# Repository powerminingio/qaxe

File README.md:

# Compatible replacement parts for ++

[25MHz Oscillator](https://www.digikey.de/de/products/detail/iqd-frequency-products/LFSPXO076024/8633951?s=N4IgTCBcDaIIwE4wGYC0cBsGAs7UDkAREAXQF8g), Replacement: [OXLTDLJANF-25.000000](https://www.digikey.de/de/products/detail/taitien/OXLTDLJANF-25-000000/13235309?srsltid=AfmBOopcMDw-7vaDW7fInywY2qr_aMaeX0WMDV0aphwuDXjSpvlEyQxF)<br/>

# Compatible replacement parts for ++ and +

[0.8V LDO](https://www.digikey.de/de/products/detail/microchip-technology/MCP1824T-0802E-OT/1635455), Replacement: [TPS78408QDBVRQ1](https://www.digikey.com/en/products/detail/texas-instruments/TPS78408QDBVRQ1/13563052)

# NerdQAxe++ Powermining revision

Few improvements for revision that we manufacture

## Features

- Car Minifuse
- 180nH inductors (Eliminates frying VRM)
- Level shifter pull-ups
- LGA115* (75x75mm) mounting pattern
- LGA2011 Narrow ILM (94x56mm) mounting pattern

**rev6.1PM**

# NerdQAxe+

NerdQaxe+ is a Qaxe+ with [Nerdminer](https://github.com/BitMaker-hub/NerdMiner_v2) / [Nerdaxe](https://github.com/BitMaker-hub/NerdAxeUltra) Display and is running the [BitAxe](https://github.com/skot/bitaxe) Firmware as its core.

It runs standalone without Raspberry Pi and uses 4 ASICs of type BM1368.

Highlights:

- uses the NerdAxe / NerdMiner display
- better Buck converter that runs a lot cooler (about 10°C) with oltage / current / power monitoring
- standalone, no Raspberry Pi or other PC needed
- AxeOS with improvements and enhancements
  - Influx DB support
  - Better charting (10m, 1h, 1d), data doesn't get lost on Web UI reloads 
  - ASIC clock and voltage adjustable without reboot
  - Stratum client stability improvements (TCP timeouts)

The NerdQAxe+ runs with a variant of the AxeOS firmware: https://github.com/shufps/ESP-Miner-NerdQAxePlus

**rev5.0** Good to go, no bug found 🥳🚀

# QAxe+

QAxe+ is a quad-BM1368 Variant. Mining speed is average 2.4TH/s at 55W (measured at 230V)<br>

<br>

**rev4:** QAxe+ with BM1368, working but ASIC reset behaves weird sometimes. Measured performance is 2.4TH/s average with 55W (measured on 230V)<br>
**rev4.1:** only change is 3 pull-down resistors on NRSTI pins<br>
<br>

# Qaxe

Qaxe is a  quad-BM1366 Miner based on the [PiAxe](https://github.com/shufps/piaxe) and [BitAxe](https://github.com/skot/bitaxe/tree/ultra-v1.3).

**rev1:** is tested and operating at about 1.7TH/s average speed.<br>
**rev2:** working fine with the expected speed of ~1.8TH/s avg after some minor modifications (330µF caps are wrongly placed, see rev3)<br>
**rev3:** Fixed Caps placement and added Boot-Switch. It should put the STM32 into DFU bootloader but not tested yet.<br>
**rev3.1:** Added pulldown on PB2 that is needed for booting the USB bootloader<br>
**rev3.2:** Board got 3mm larger for a perfect fit of low-profile coolers<br>
<br>
**note**: If you have a board with `BOOT`-button (any rev3) please order the L072 STM32 (BOM has been updated) because usb bootloader is the easiest way to flash the STM.<br>

ASICs
=====

The QAxe uses 4 ASICs of type BM1366.

The QAxe+ and NerdQaxe+ uses 4 ASICs of type BM1368.

Compilation (Bootloader or CMSIS-DAP) (QAxe, QAxe+)
======================================

## Dockered compilation and flashing
There is a wonderfull Docker based single-script compilation and flash tool for the QAxe Firmware:

https://github.com/AnimaI/QAxe-Docker-Bootloader

## Manual compilation and installation

```bash
# install curl
sudo apt install curl

# install rust
curl --proto '=https' --tlsv1.2 https://sh.rustup.rs -sSf | sh

# add to ~/.bash.rc (afterwards, opening a new terminal is needed)
echo 'source "$HOME/.cargo/env"' >> ~/.bashrc

# clone repository
git clone https://github.com/shufps/qaxe

# clone submodules
cd qaxe
git submodule init
git submodule update

# add rust target for STM32L0 variants
rustup target add thumbv6m-none-eabi

# or add rust target for STM32L1 variants
#rustup target add thumbv7m-none-eabi

# build firmware for L072
cd firmware/fw-L072CB
./build.sh
```

## Installation via USB Bootloader on board with `BOOT` button (QAxe, QAxe+)
The STM32L072CB variant has an integrated DFU Bootloader that starts when pressing the `BOOT` button during reset.

Afterwards the firmware can be flashed via `dfu-utils`:

```bash
# install cargo-binutils and llvm tools
cargo install cargo-binutils
rustup component add llvm-tools-preview

# create the firmware.bin
DEFMT_LOG=info cargo objcopy --release --bin qaxe -- -O binary qaxe.bin

# install dfu-utils
sudo apt-get install dfu-util

now start the stm32 in DFU mode by pressing `boot` (only works with the STM32L072CB variant)

# after booting, list the devices
dfu-util --list

# flash the binary
dfu-util -a 0 -s 0x08000000:leave -D qaxe.bin
```

Mining Client (QAxe, QAxe+)
=============

Stratum Mining Client:<br>
https://github.com/shufps/piaxe-miner

Misc
====
If you like this project and want to support future work, feel free to donate to:
`bc1q7n70rumyv6lvu8avpml0c3uggvssfu52egum3q`

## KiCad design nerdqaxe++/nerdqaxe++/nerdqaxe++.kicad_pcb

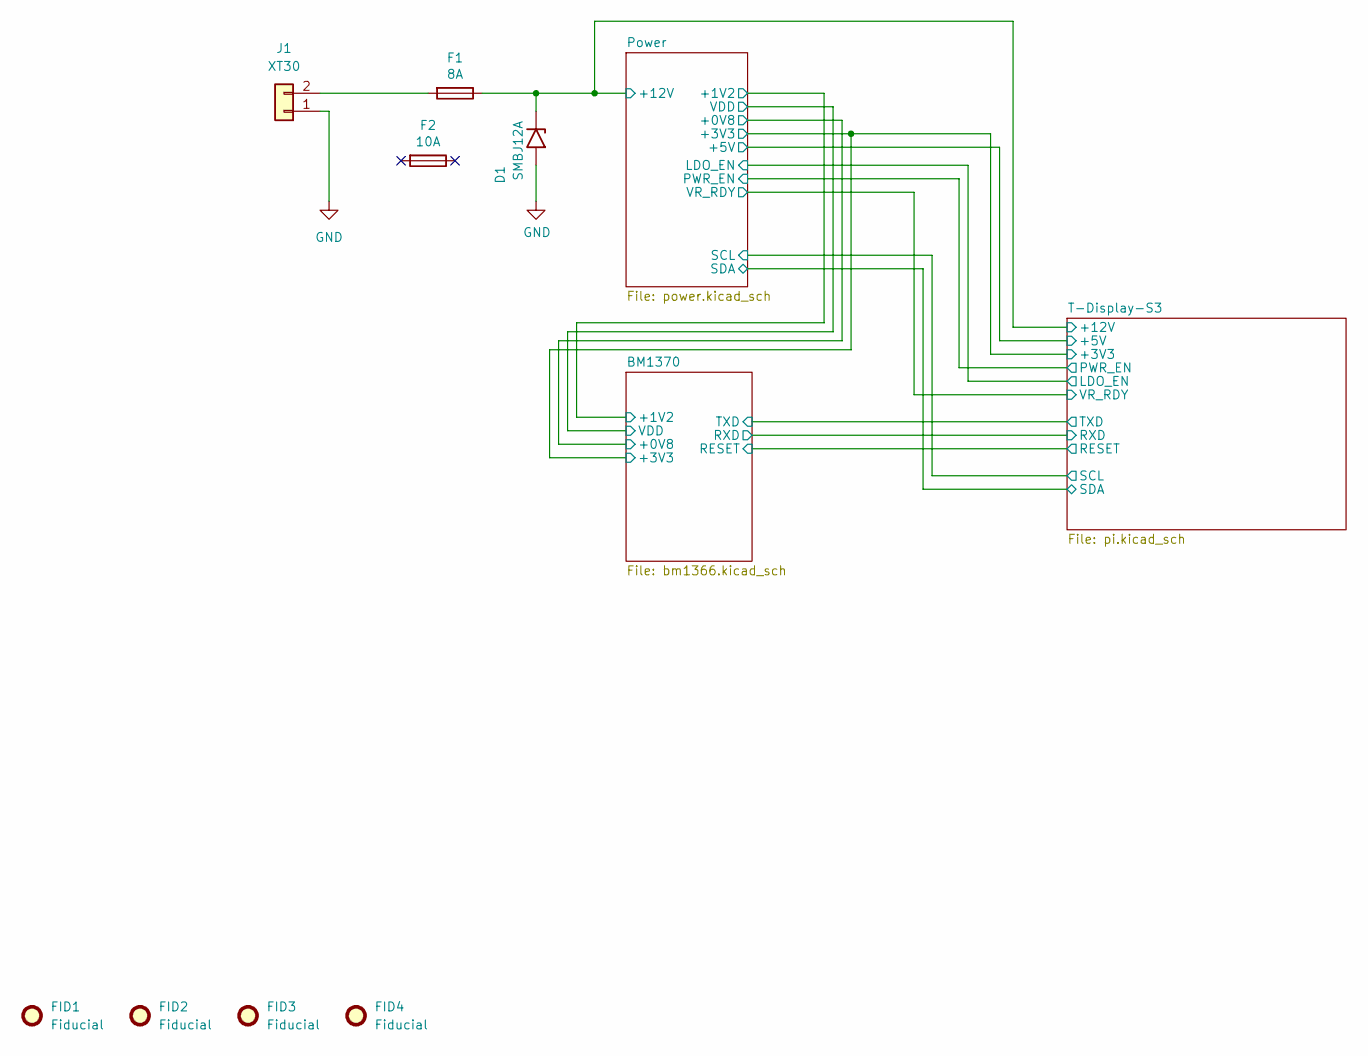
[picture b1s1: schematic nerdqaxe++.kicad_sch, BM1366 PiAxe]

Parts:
D1: SMBJ12A; D_SMB
F1: 8A; Fuseholder_Blade_Mini_Keystone_3568
F2: 10A
FID1, FID2, FID3, FID4: Fiducial; Fiducial_1mm_Mask2mm
J1: XT30; AMASS_XT30PW-M_1x02_P2.50mm_Horizontal

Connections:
+12V: D1.1 (A1), F1.1; also elsewhere on the board
GND: D1.2 (A2), J1.1; also elsewhere on the board
unnamed: F1.2, J1.2

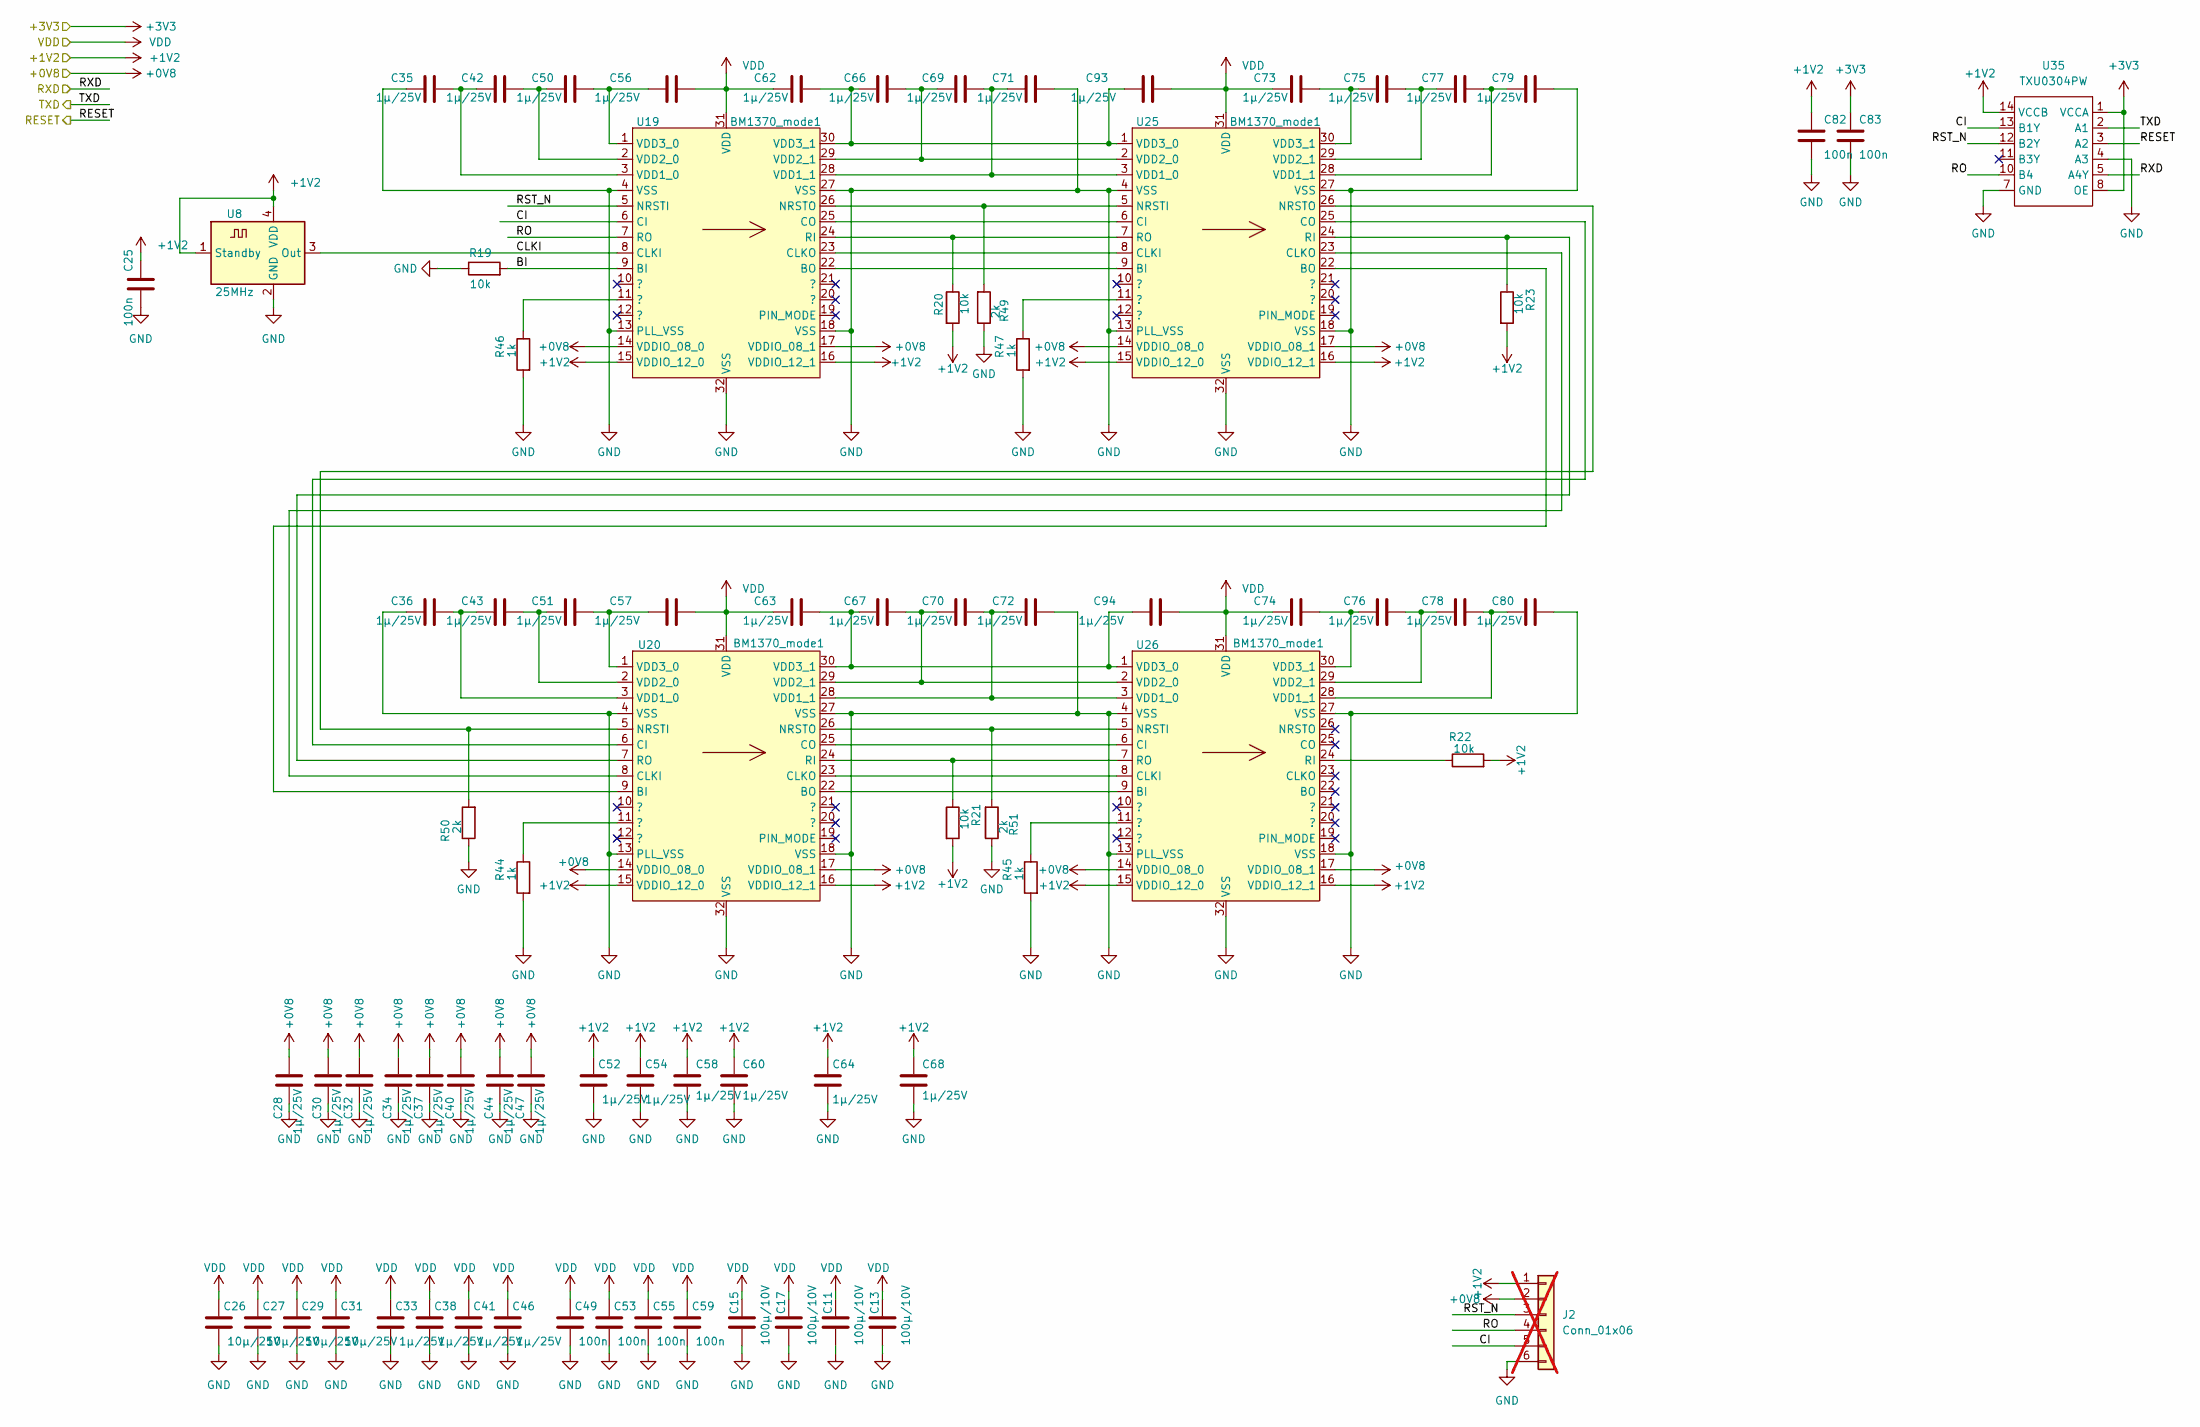
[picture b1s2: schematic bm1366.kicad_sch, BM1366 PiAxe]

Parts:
C11, C13, C15, C17: 100µ/10V; C_1210_3225Metric
C25, C49, C53, C55, C59, C82, C83: 100n; C_0805_2012Metric
C26, C27, C29, C31: 10µ/25V; C_0805_2012Metric
C28, C30, C32, C33, C34, C35, C36, C37, C38, C40, C41, C42, C43, C44, C46, C47, C50, C51, C52, C54, C56, C57, C58, C60, C62, C63, C64, C66, C67, C68, C69, C70, C71, C72, C73, C74, C75, C76, C77, C78, C79, C80, C93, C94: 1µ/25V; C_0805_2012Metric
J2: Conn_01x06; PinHeader_1x06_P1.27mm_Vertical; not fitted
R19, R20, R21, R22, R23: 10k; R_0805_2012Metric
R44, R45, R46, R47: 1k; R_0805_2012Metric
R49, R50, R51: 2k; R_0805_2012Metric
U8: 25MHz; Oscillator_SMD_EuroQuartz_XO32-4Pin_3.2x2.5mm
U19, U20, U25, U26: BM1370_mode1; BM1370_JB
U35: TXU0304PW; TSSOP-14_4.4x5mm_P0.65mm

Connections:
+0V8: C28.2, C30.2, C32.2, C34.2, C37.2, C40.2, C44.2, C47.2, J2.2, U19.14 (VDDIO_08_0), U19.17 (VDDIO_08_1), U20.14 (VDDIO_08_0), U20.17 (VDDIO_08_1), U25.14 (VDDIO_08_0), U25.17 (VDDIO_08_1), U26.14 (VDDIO_08_0), U26.17 (VDDIO_08_1); also elsewhere on the board
+1V2: C25.1, C52.1, C54.1, C58.1, C60.1, C64.1, C68.1, C82.1, J2.1, R20.2, R21.2, R22.2, R23.2, U8.1 (Standby), U8.4 (VDD), U19.15 (VDDIO_12_0), U19.16 (VDDIO_12_1), U20.15 (VDDIO_12_0), U20.16 (VDDIO_12_1), U25.15 (VDDIO_12_0), U25.16 (VDDIO_12_1), U26.15 (VDDIO_12_0), U26.16 (VDDIO_12_1), U35.14 (VCCB); also elsewhere on the board
+3V3: C83.1, U35.1 (VCCA), U35.8 (OE); also elsewhere on the board
/BM1370/BI: R19.2, U19.9 (BI)
/BM1370/CI: J2.5, U19.6 (CI), U35.13 (B1Y)
/BM1370/CLKI: U8.3 (Out), U19.8 (CLKI)
/BM1370/RESET: U35.3 (A2); also elsewhere on the board
/BM1370/RO: J2.4, U19.7 (RO), U35.10 (B4)
/BM1370/RST_N: J2.3, U19.5 (NRSTI), U35.12 (B2Y)
/BM1370/RXD: U35.5 (A4Y); also elsewhere on the board
/BM1370/TXD: U35.2 (A1); also elsewhere on the board
GND: C11.2, C13.2, C15.2, C17.2, C25.2, C26.2, C27.2, C28.1, C29.2, C30.1, C31.2, C32.1, C33.2, C34.1, C35.1, C36.1, C37.1, C38.2, C40.1, C41.2, C44.1, C46.2, C47.1, C49.2, C52.2, C53.2, C54.2, C55.2, C58.2, C59.2, C60.2, C64.2, C68.2, C71.2, C72.2, C79.2, C80.2, C82.2, C83.2, J2.6, R19.1, R44.2, R45.2, R46.2, R47.2, R49.1, R50.1, R51.1, U8.2 (GND), U19.4 (VSS), U19.13 (PLL_VSS), U19.18 (VSS), U19.27 (VSS), U19.32 (VSS), U20.4 (VSS), U20.13 (PLL_VSS), U20.18 (VSS), U20.27 (VSS), U20.32 (VSS), U25.4 (VSS), U25.13 (PLL_VSS), U25.18 (VSS), U25.27 (VSS), U25.32 (VSS), U26.4 (VSS), U26.13 (PLL_VSS), U26.18 (VSS), U26.27 (VSS), U26.32 (VSS), U35.4 (A3), U35.7 (GND); also elsewhere on the board
unnamed: R44.1, U20.11 (?)
unnamed: R45.1, U26.11 (?)
unnamed: R46.1, U19.11 (?)
unnamed: R47.1, U25.11 (?)
unnamed: U19.22 (BO), U25.9 (BI)
unnamed: U19.23 (CLKO), U25.8 (CLKI)
unnamed: U19.25 (CO), U25.6 (CI)
unnamed: R49.2, U19.26 (NRSTO), U25.5 (NRSTI)
unnamed: R20.1, U19.24 (RI), U25.7 (RO)
unnamed: C35.2, C42.1, U19.3 (VDD1_0)
unnamed: C69.2, C71.1, U19.28 (VDD1_1), U25.3 (VDD1_0)
unnamed: C42.2, C50.1, U19.2 (VDD2_0)
unnamed: C66.2, C69.1, U19.29 (VDD2_1), U25.2 (VDD2_0)
unnamed: C50.2, C56.1, U19.1 (VDD3_0)
unnamed: C62.2, C66.1, C93.1, U19.30 (VDD3_1), U25.1 (VDD3_0)
unnamed: U20.9 (BI), U25.22 (BO)
unnamed: U20.22 (BO), U26.9 (BI)
unnamed: U20.6 (CI), U25.25 (CO)
unnamed: U20.8 (CLKI), U25.23 (CLKO)
unnamed: U20.23 (CLKO), U26.8 (CLKI)
unnamed: U20.25 (CO), U26.6 (CI)
unnamed: R50.2, U20.5 (NRSTI), U25.26 (NRSTO)
unnamed: R51.2, U20.26 (NRSTO), U26.5 (NRSTI)
unnamed: R21.1, U20.24 (RI), U26.7 (RO)
unnamed: R23.1, U20.7 (RO), U25.24 (RI)
unnamed: C36.2, C43.1, U20.3 (VDD1_0)
unnamed: C70.2, C72.1, U20.28 (VDD1_1), U26.3 (VDD1_0)
unnamed: C43.2, C51.1, U20.2 (VDD2_0)
unnamed: C67.2, C70.1, U20.29 (VDD2_1), U26.2 (VDD2_0)
unnamed: C51.2, C57.1, U20.1 (VDD3_0)
unnamed: C63.2, C67.1, C94.1, U20.30 (VDD3_1), U26.1 (VDD3_0)
unnamed: C77.2, C79.1, U25.28 (VDD1_1)
unnamed: C75.2, C77.1, U25.29 (VDD2_1)
unnamed: C73.2, C75.1, U25.30 (VDD3_1)
unnamed: R22.1, U26.24 (RI)
unnamed: C78.2, C80.1, U26.28 (VDD1_1)
unnamed: C76.2, C78.1, U26.29 (VDD2_1)
unnamed: C74.2, C76.1, U26.30 (VDD3_1)
VDD: C11.1, C13.1, C15.1, C17.1, C26.1, C27.1, C29.1, C31.1, C33.1, C38.1, C41.1, C46.1, C49.1, C53.1, C55.1, C56.2, C57.2, C59.1, C62.1, C63.1, C73.1, C74.1, C93.2, C94.2, U19.31 (VDD), U20.31 (VDD), U25.31 (VDD), U26.31 (VDD); also elsewhere on the board

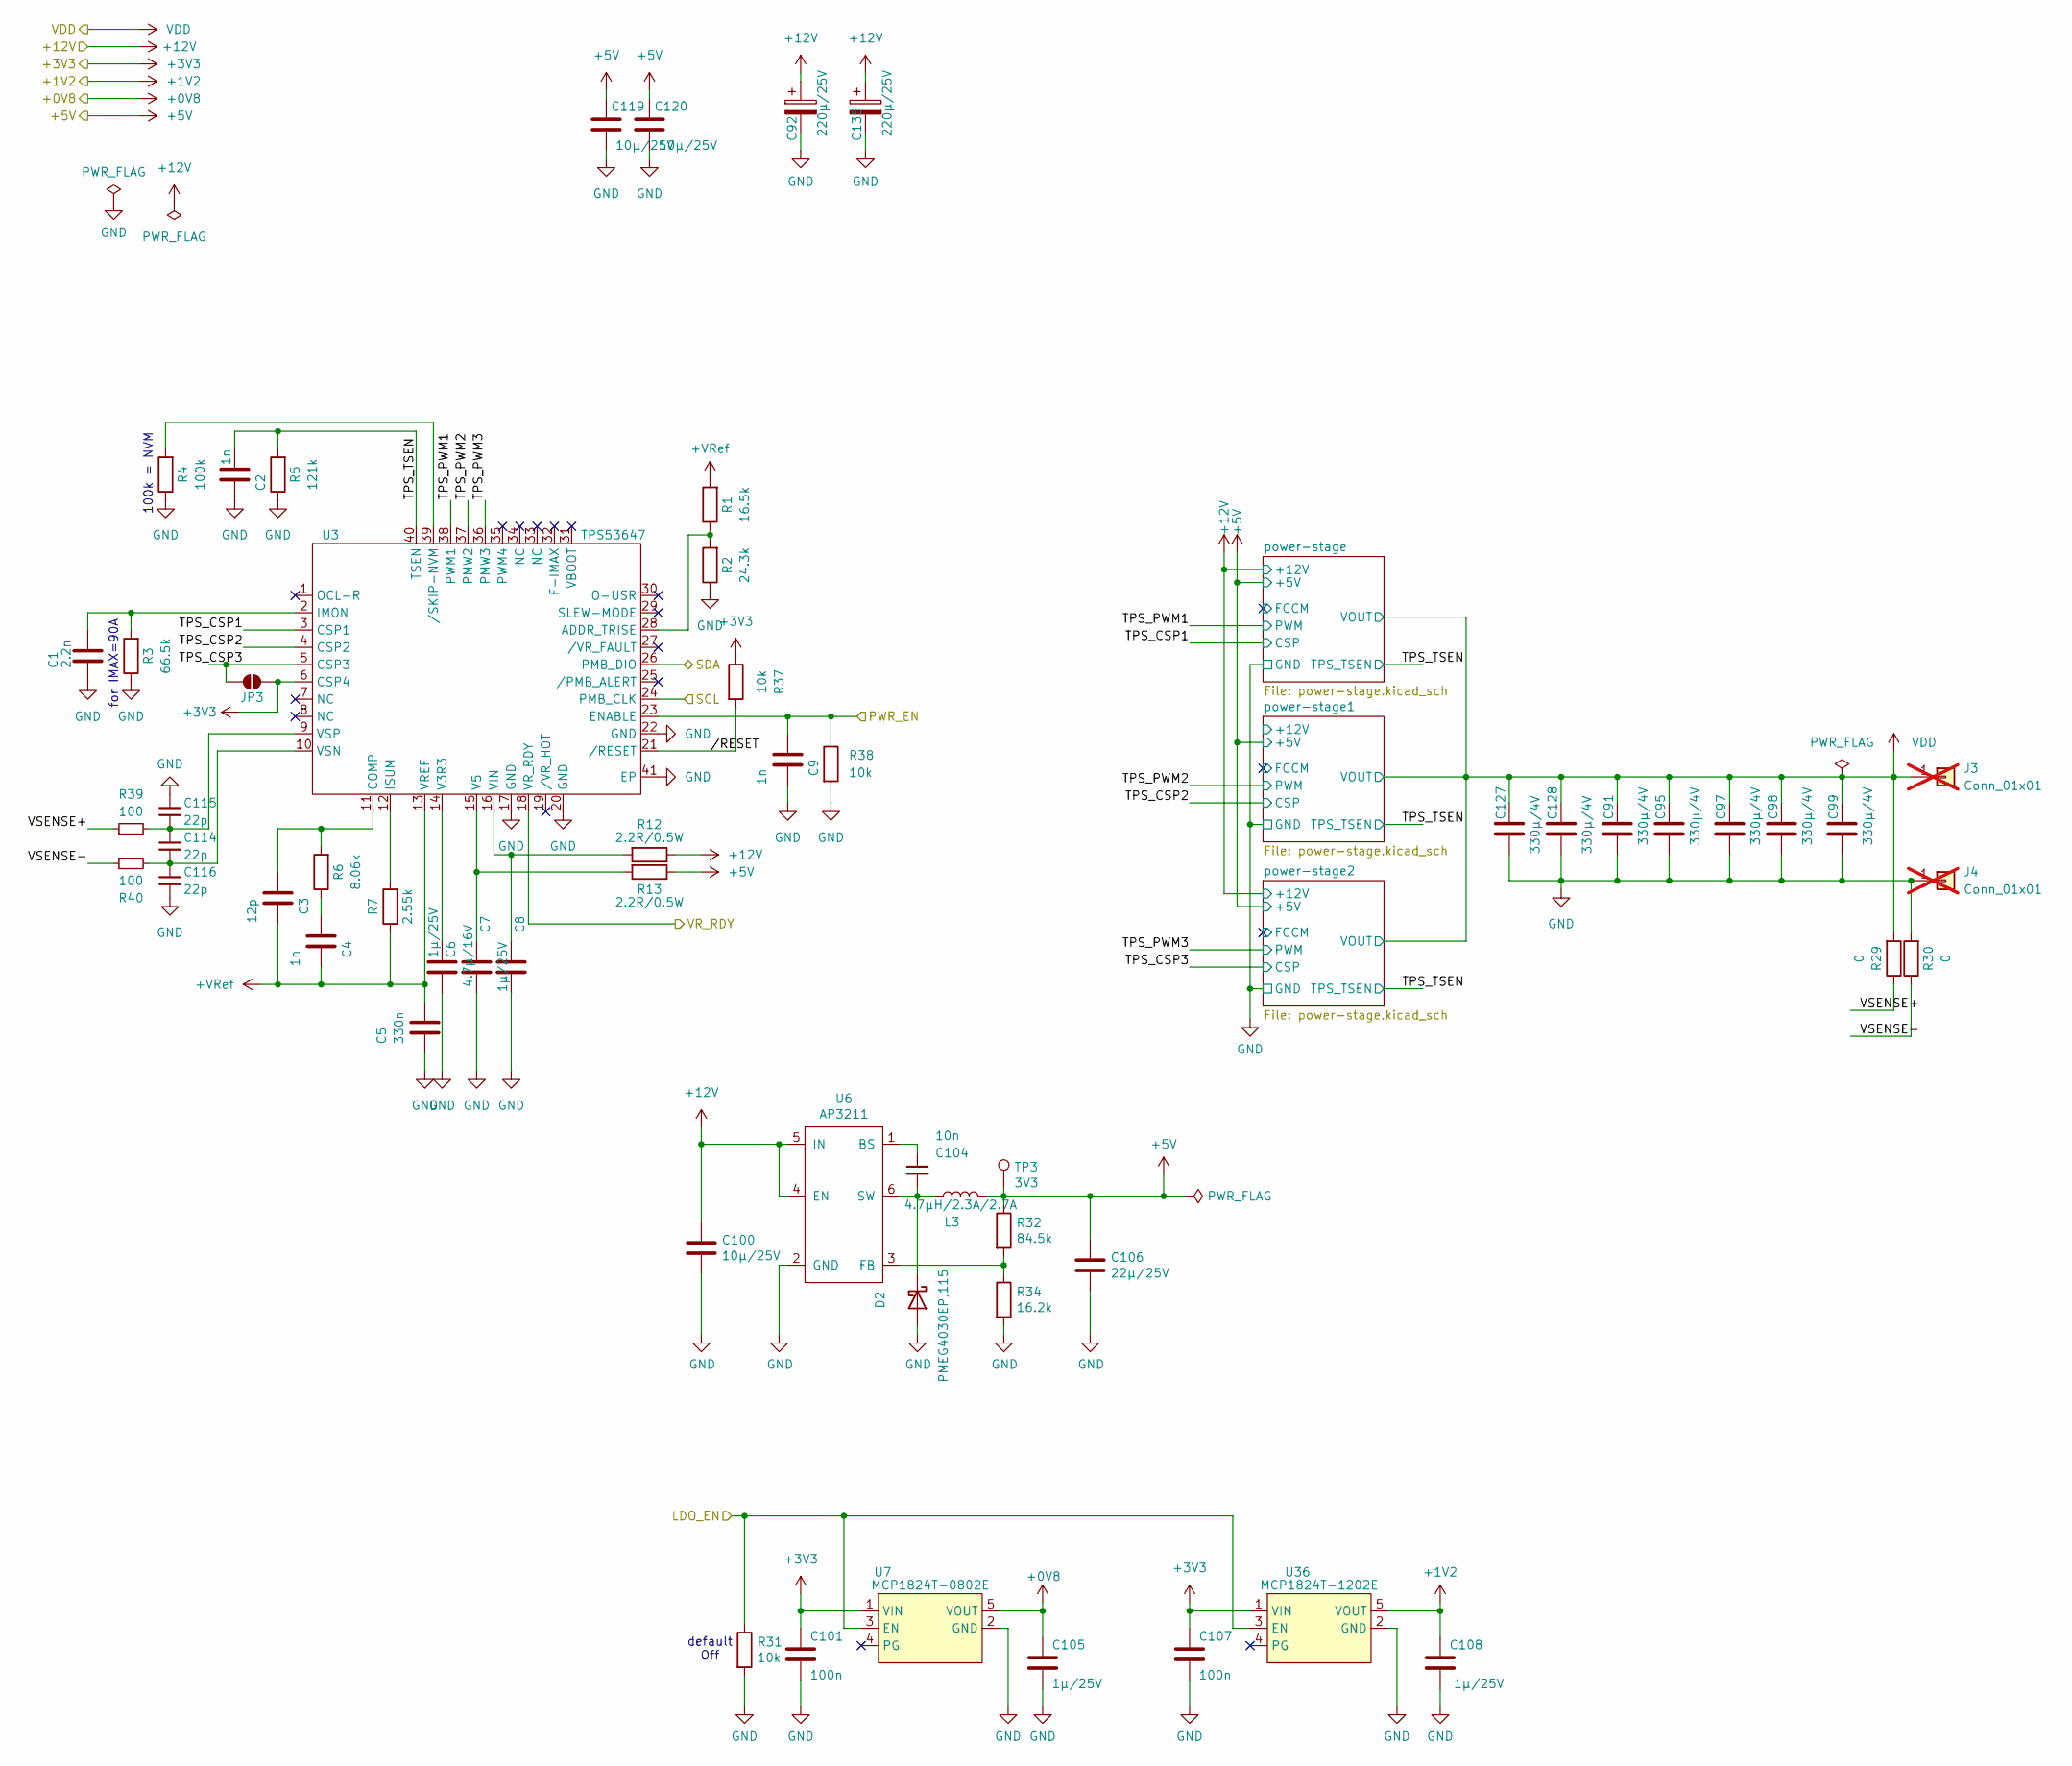
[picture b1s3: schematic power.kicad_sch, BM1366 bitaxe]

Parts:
C1: 2.2n; C_0805_2012Metric
C2, C4, C9: 1n; C_0805_2012Metric
C3: 12p; C_0603_1608Metric
C5: 330n; C_0805_2012Metric
C6, C8, C105, C108: 1µ/25V; C_0805_2012Metric
C7: 4.7µ/16V; C_0805_2012Metric
C91, C95, C97, C98, C99, C127, C128: 330µ/4V; C_1210_3225Metric
C92, C135: 220µ/25V; CP_Elec_8x10
C100, C119, C120: 10µ/25V; C_0805_2012Metric
C101, C107: 100n; C_0805_2012Metric
C104: 10n; C_0805_2012Metric
C106: 22µ/25V; C_1210_3225Metric
C114, C115, C116: 22p; C_0603_1608Metric
D2: PMEG4030EP,115; D_SOD-128
J3, J4: Conn_01x01; Wuerth_REDCUBE-THR_WP-THRBU_74650194_THR; not fitted
JP3: SolderJumper_2_Open; SolderJumper-2_P1.3mm_Open_RoundedPad1.0x1.5mm
L3: 4.7µH/2.3A/2.7A; L_Taiyo-Yuden_NR-50xx
R1: 16.5k; R_0805_2012Metric
R2: 24.3k; R_0805_2012Metric
R3: 66.5k; R_0805_2012Metric
R4: 100k; R_0805_2012Metric
R5: 121k; R_0805_2012Metric
R6: 8.06k; R_0805_2012Metric
R7: 2.55k; R_0805_2012Metric
R12, R13: 2.2R/0.5W; R_0805_2012Metric
R29, R30: 0; R_0805_2012Metric
R31, R37, R38: 10k; R_0805_2012Metric
R32: 84.5k; R_0805_2012Metric
R34: 16.2k; R_0805_2012Metric
R39, R40: 100; R_0805_2012Metric
TP3: 3V3; TestPoint_Pad_2.0x2.0mm
U3: TPS53647; Texas_RHA0040B_VQFN-40-1EP_6x6mm_P0.5mm_EP4.15x4.15mm_Therm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
U6: AP3211; SOT-23-6
U7: MCP1824T-0802E; SOT-23-5
U36: MCP1824T-1202E; SOT-23-5

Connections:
+0V8: C105.1, U7.5 (VOUT); also elsewhere on the board
+1V2: C108.1, U36.5 (VOUT); also elsewhere on the board
+3V3: C101.1, C107.1, JP3.2 (B), R37.1, U3.6 (CSP4), U7.1 (VIN), U36.1 (VIN); also elsewhere on the board
+5V: C106.1, C119.1, C120.1, L3.2, R13.1, R32.1, TP3.1; also elsewhere on the board
+12V: C92.1, C100.1, C135.1, R12.1, U6.4 (EN), U6.5 (IN); also elsewhere on the board
+VRef: C3.2, C4.2, C5.1, R1.2, R7.1, U3.13 (VREF); also elsewhere on the board
/Power/LDO_EN: R31.1, U7.3 (EN), U36.3 (EN); also elsewhere on the board
/Power/PWR_EN: C9.1, R38.1, U3.23 (ENABLE); also elsewhere on the board
/Power/TPS_CSP1: U3.3 (CSP1); also elsewhere on the board
/Power/TPS_CSP2: U3.4 (CSP2); also elsewhere on the board
/Power/TPS_CSP3: JP3.1 (A), U3.5 (CSP3); also elsewhere on the board
/Power/TPS_PWM1: U3.38 (PWM1); also elsewhere on the board
/Power/TPS_PWM2: U3.37 (PMW2); also elsewhere on the board
/Power/TPS_PWM3: U3.36 (PMW3); also elsewhere on the board
/Power/TPS_TSEN: C2.1, R5.2, U3.40 (TSEN); also elsewhere on the board
/Power/VR_RDY: U3.18 (VR_RDY); also elsewhere on the board
/Power/VSENSE+: R29.1, R39.1
/Power/VSENSE-: R30.1, R40.1
/Power//RESET: R37.2, U3.21 (/RESET)
/T-Display-S3/SCL: U3.24 (PMB_CLK); also elsewhere on the board
/T-Display-S3/SDA: U3.26 (PMB_DIO); also elsewhere on the board
GND: C1.2, C2.2, C5.2, C6.2, C7.1, C8.1, C9.2, C91.2, C92.2, C95.2, C97.2, C98.2, C99.2, C100.2, C101.2, C105.2, C106.2, C107.2, C108.2, C115.1, C116.2, C119.2, C120.2, C127.2, C128.2, C135.2, D2.2 (A), J4.1, R2.1, R3.1, R4.1, R5.1, R30.2, R31.2, R34.2, R38.2, U3.17 (GND), U3.20 (GND), U3.22 (GND), U3.41 (EP), U6.2 (GND), U7.2 (GND), U36.2 (GND); also elsewhere on the board
unnamed: C4.1, R6.1
unnamed: C104.2, D2.1 (K), L3.1, U6.6 (SW)
unnamed: R1.1, R2.2, U3.28 (ADDR_TRISE)
unnamed: C3.1, R6.2, U3.11 (COMP)
unnamed: C1.1, R3.2, U3.2 (IMON)
unnamed: R7.2, U3.12 (ISUM)
unnamed: C6.1, U3.14 (V3R3)
unnamed: C7.2, R13.2, U3.15 (V5)
unnamed: C8.2, R12.2, U3.16 (VIN)
unnamed: C114.2, C116.1, R40.2, U3.10 (VSN)
unnamed: C114.1, C115.2, R39.2, U3.9 (VSP)
unnamed: R4.2, U3.39 (/SKIP-NVM)
unnamed: C104.1, U6.1 (BS)
unnamed: R32.2, R34.1, U6.3 (FB)
VDD: C91.1, C95.1, C97.1, C98.1, C99.1, C127.1, C128.1, J3.1, R29.2; also elsewhere on the board

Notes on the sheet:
default Off
for IMAX=90A
100k = NVM

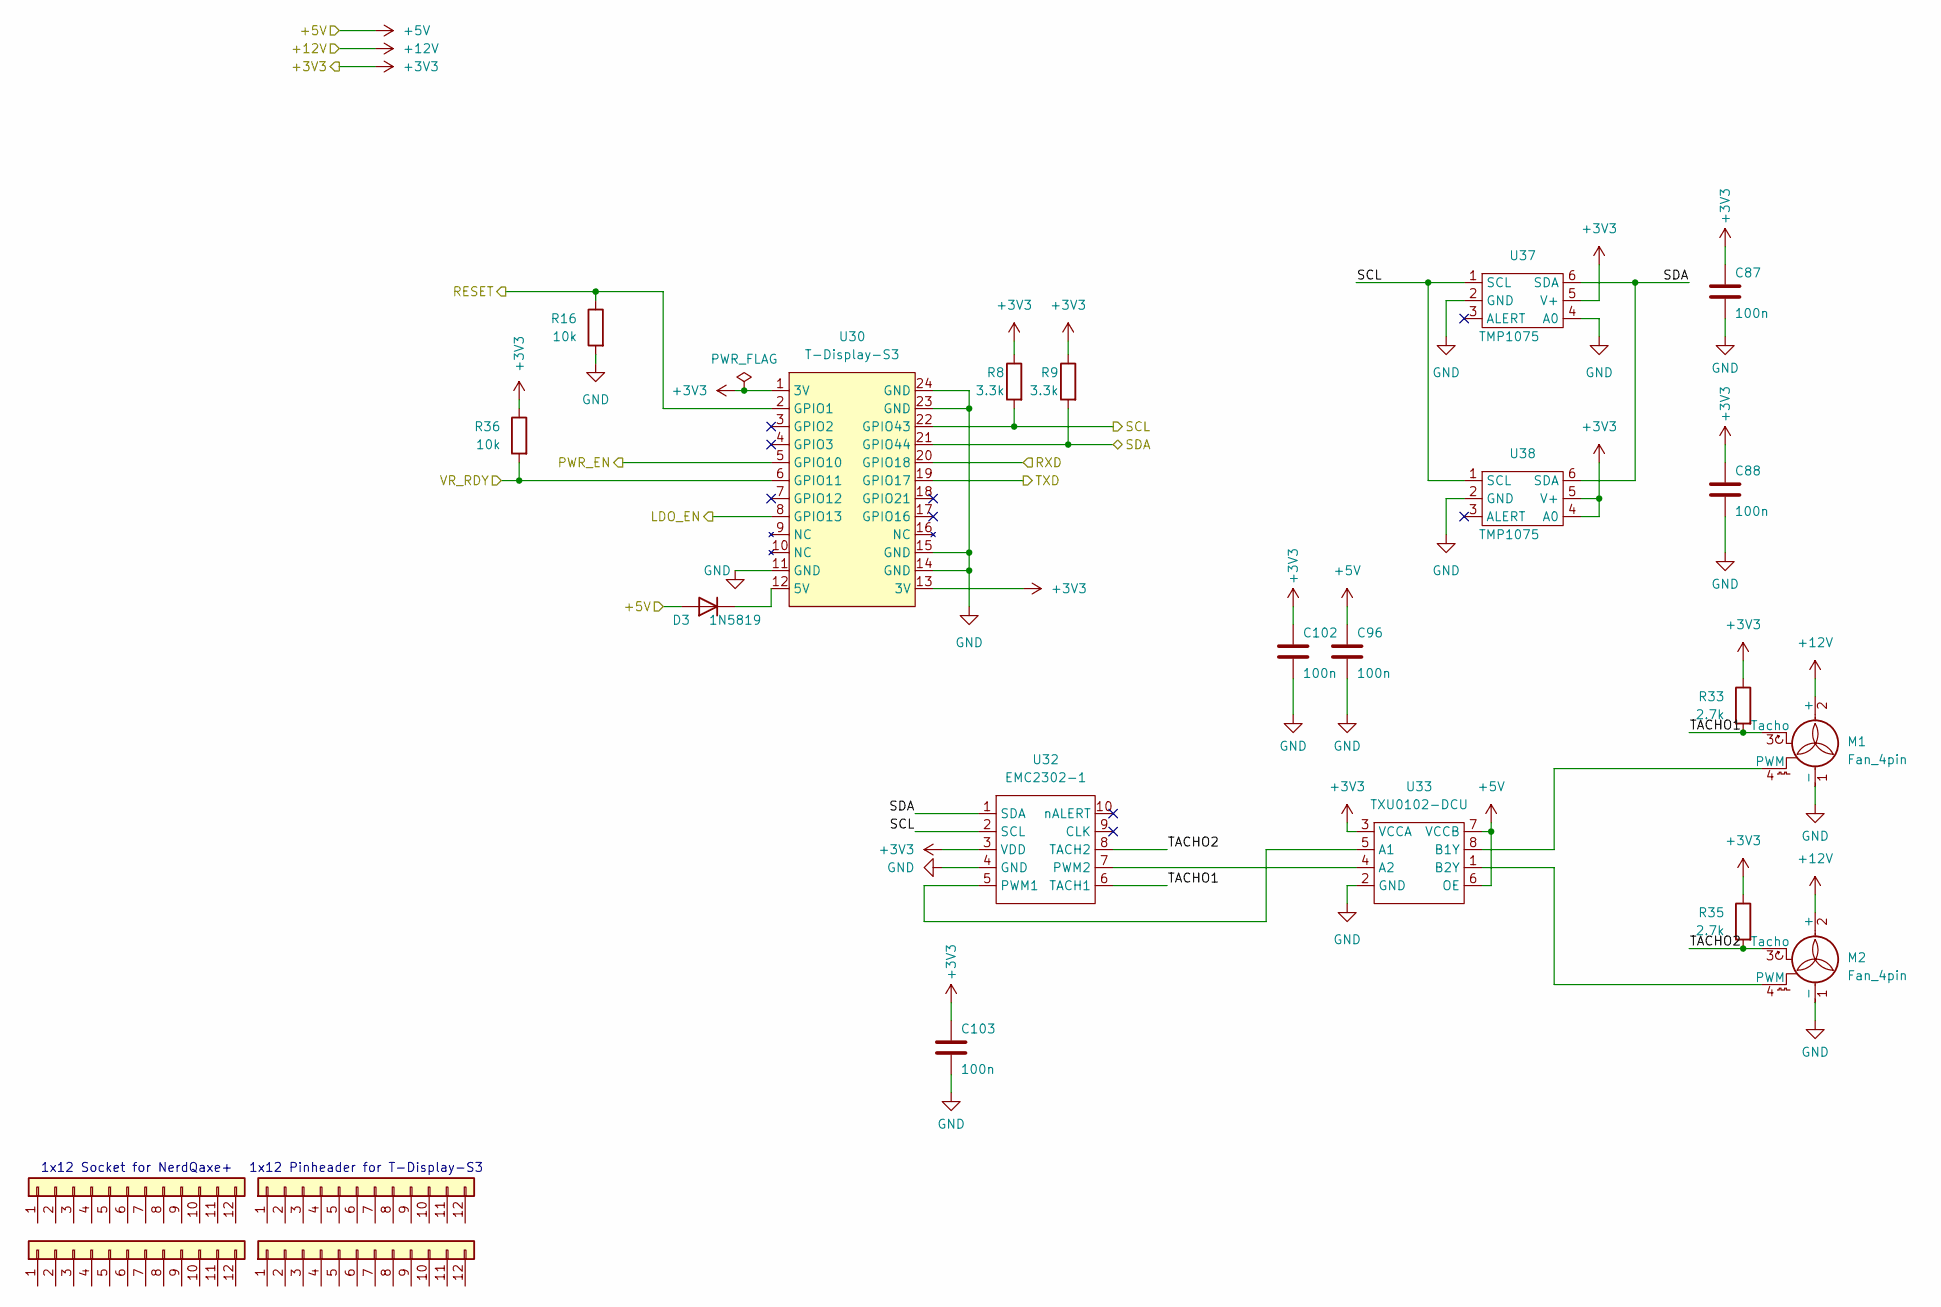
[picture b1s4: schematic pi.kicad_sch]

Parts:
C87, C88, C96, C102, C103: 100n; C_0805_2012Metric
D3: 1N5819; D_SOD-123
J5, J6: Conn_01x12-Socket
J7, J8: Conn_01x12-Header
M1, M2: Fan_4pin; FanPinHeader_1x04_P2.54mm_Vertical
R8, R9: 3.3k; R_0805_2012Metric
R16, R36: 10k; R_0805_2012Metric
R33, R35: 2.7k; R_0805_2012Metric
U30: T-Display-S3
U32: EMC2302-1; MSOP-10_3x3mm_P0.5mm
U33: TXU0102-DCU; VSSOP-8_2.3x2mm_P0.5mm
U37, U38: TMP1075; TMP1075-DRL

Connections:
+3V3: C87.1, C88.1, C102.1, C103.1, R8.1, R9.1, R33.1, R35.1, R36.1, U30.1 (3V), U30.13 (3V), U32.3 (VDD), U33.3 (VCCA), U37.5 (V+), U38.4 (A0), U38.5 (V+); also elsewhere on the board
+5V: C96.1, D3.2 (A), U33.6 (OE), U33.7 (VCCB); also elsewhere on the board
+12V: M1.2 (+), M2.2 (+); also elsewhere on the board
/BM1370/RESET: R16.1, U30.2 (GPIO1); also elsewhere on the board
/BM1370/RXD: U30.20 (GPIO18); also elsewhere on the board
/BM1370/TXD: U30.19 (GPIO17); also elsewhere on the board
/Power/LDO_EN: U30.8 (GPIO13); also elsewhere on the board
/Power/PWR_EN: U30.5 (GPIO10); also elsewhere on the board
/Power/VR_RDY: R36.2, U30.6 (GPIO11); also elsewhere on the board
/T-Display-S3/SCL: R8.2, U30.22 (GPIO43), U32.2 (SCL), U37.1 (SCL), U38.1 (SCL); also elsewhere on the board
/T-Display-S3/SDA: R9.2, U30.21 (GPIO44), U32.1 (SDA), U37.6 (SDA), U38.6 (SDA); also elsewhere on the board
/T-Display-S3/TACHO1: M1.3 (Tacho), R33.2, U32.6 (TACH1)
/T-Display-S3/TACHO2: M2.3 (Tacho), R35.2, U32.8 (TACH2)
GND: C87.2, C88.2, C96.2, C102.2, C103.2, M1.1 (-), M2.1 (-), R16.2, U30.11 (GND), U30.14 (GND), U30.15 (GND), U30.23 (GND), U30.24 (GND), U32.4 (GND), U33.2 (GND), U37.2 (GND), U37.4 (A0), U38.2 (GND); also elsewhere on the board
unnamed: D3.1 (K), U30.12 (5V)
unnamed: M1.4 (PWM), U33.8 (B1Y)
unnamed: M2.4 (PWM), U33.1 (B2Y)
unnamed: U32.5 (PWM1), U33.5 (A1)
unnamed: U32.7 (PWM2), U33.4 (A2)

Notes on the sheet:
1x12 Socket for NerdQaxe+
1x12 Pinheader for T-Display-S3

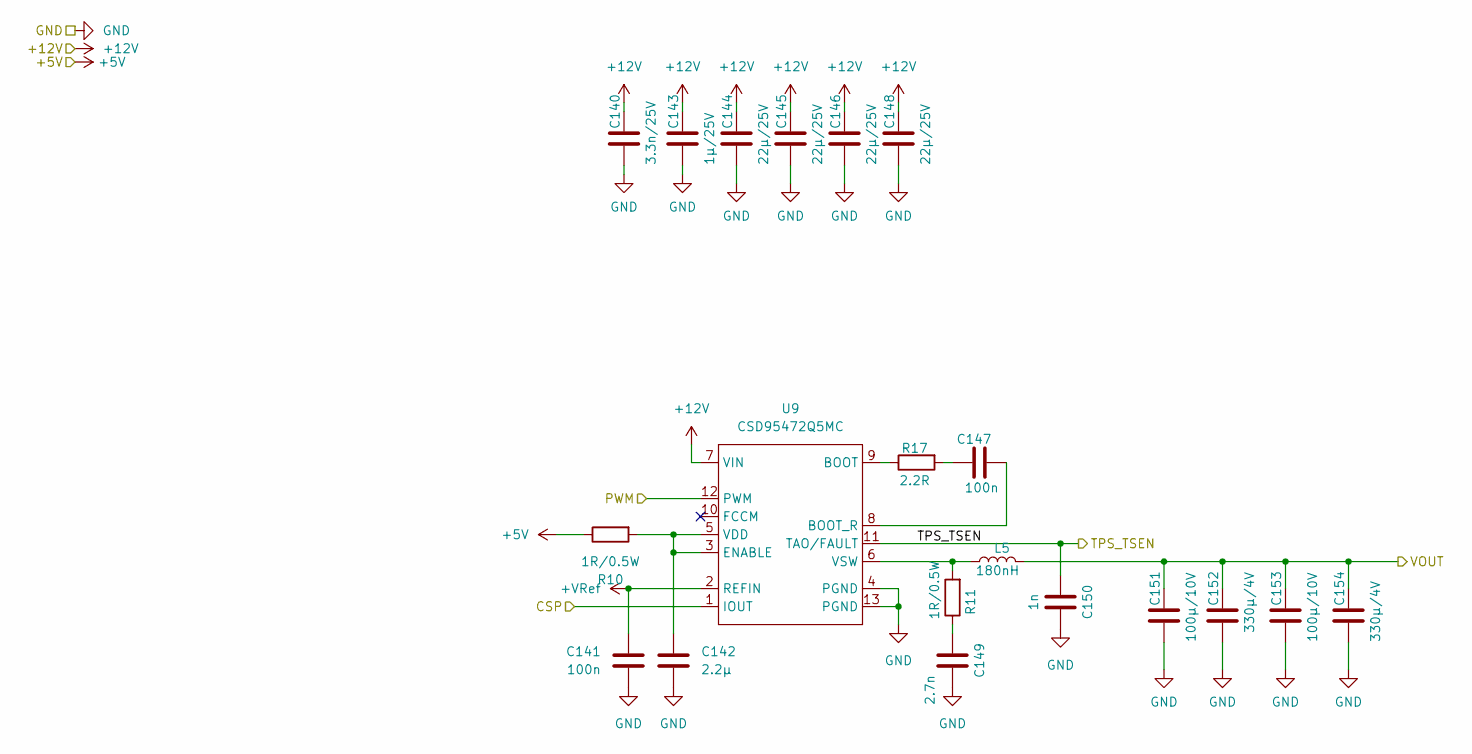
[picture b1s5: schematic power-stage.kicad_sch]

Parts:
C140: 3.3n/25V; C_0805_2012Metric
C141: 100n; C_0805_2012Metric
C142: 2.2µ; C_0805_2012Metric
C143: 1µ/25V; C_0805_2012Metric
C144, C145, C146, C148: 22µ/25V; C_1210_3225Metric
C147: 100n; C_0603_1608Metric
C149: 2.7n; C_0805_2012Metric
C150: 1n; C_0805_2012Metric
C151, C153: 100µ/10V; C_1210_3225Metric
C152, C154: 330µ/4V; C_1210_3225Metric
L5: 180nH; PA5187181HLT
R10, R11: 1R/0.5W; R_0805_2012Metric
R17: 2.2R; R_0603_1608Metric
U9: CSD95472Q5MC

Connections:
+5V: R10.1; also elsewhere on the board
+12V: C140.1, C143.1, C144.1, C145.1, C146.1, C148.1, U9.7 (VIN); also elsewhere on the board
+VRef: C141.1, U9.2 (REFIN); also elsewhere on the board
/Power/TPS_CSP2: U9.1 (IOUT); also elsewhere on the board
/Power/TPS_PWM2: U9.12 (PWM); also elsewhere on the board
/Power/TPS_TSEN: C150.1, U9.11 (TAO/FAULT); also elsewhere on the board
GND: C140.2, C141.2, C142.2, C143.2, C144.2, C145.2, C146.2, C148.2, C149.2, C150.2, C151.2, C152.2, C153.2, C154.2, U9.4 (PGND), U9.13 (PGND); also elsewhere on the board
unnamed: C147.1, R17.2
unnamed: C149.1, R11.1
unnamed: R17.1, U9.9 (BOOT)
unnamed: C147.2, U9.8 (BOOT_R)
unnamed: C142.1, R10.2, U9.3 (ENABLE), U9.5 (VDD)
unnamed: L5.1, R11.2, U9.6 (VSW)
VDD: C151.1, C152.1, C153.1, C154.1, L5.2; also elsewhere on the board

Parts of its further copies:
C10, C156: 100n; C_0805_2012Metric
C12, C157: 2.2µ; C_0805_2012Metric
C14, C162: 100n; C_0603_1608Metric
C18, C164: 2.7n; C_0805_2012Metric
C20, C23, C81, C89, C159, C160, C161, C163: 22µ/25V; C_1210_3225Metric
C21, C24, C166, C168: 100µ/10V; C_1210_3225Metric
C86, C90, C167, C169: 330µ/4V; C_1210_3225Metric
C109, C165: 1n; C_0805_2012Metric
C117, C155: 3.3n/25V; C_0805_2012Metric
C118, C158: 1µ/25V; C_0805_2012Metric
L1, L6: 180nH; PA5187181HLT
R14, R15, R25, R27: 1R/0.5W; R_0805_2012Metric
R18, R24: 2.2R; R_0603_1608Metric
U4, U10: CSD95472Q5MC

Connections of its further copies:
+5V: R14.1, R25.1; also elsewhere on the board
+12V: C20.1, C23.1, C81.1, C89.1, C117.1, C118.1, C155.1, C158.1, C159.1, C160.1, C161.1, C163.1, U4.7 (VIN), U10.7 (VIN); also elsewhere on the board
+VRef: C10.1, C156.1, U4.2 (REFIN), U10.2 (REFIN); also elsewhere on the board
/Power/TPS_CSP1: U4.1 (IOUT); also elsewhere on the board
/Power/TPS_CSP3: U10.1 (IOUT); also elsewhere on the board
/Power/TPS_PWM1: U4.12 (PWM); also elsewhere on the board
/Power/TPS_PWM3: U10.12 (PWM); also elsewhere on the board
/Power/TPS_TSEN: C109.1, C165.1, U4.11 (TAO/FAULT), U10.11 (TAO/FAULT); also elsewhere on the board
GND: C10.2, C12.2, C18.2, C20.2, C21.2, C23.2, C24.2, C81.2, C86.2, C89.2, C90.2, C109.2, C117.2, C118.2, C155.2, C156.2, C157.2, C158.2, C159.2, C160.2, C161.2, C163.2, C164.2, C165.2, C166.2, C167.2, C168.2, C169.2, U4.4 (PGND), U4.13 (PGND), U10.4 (PGND), U10.13 (PGND); also elsewhere on the board
unnamed: C14.1, R18.2
unnamed: C18.1, R27.1
unnamed: C162.1, R24.2
unnamed: C164.1, R15.1
unnamed: R18.1, U4.9 (BOOT)
unnamed: C14.2, U4.8 (BOOT_R)
unnamed: C12.1, R25.2, U4.3 (ENABLE), U4.5 (VDD)
unnamed: L1.1, R27.2, U4.6 (VSW)
unnamed: R24.1, U10.9 (BOOT)
unnamed: C162.2, U10.8 (BOOT_R)
unnamed: C157.1, R14.2, U10.3 (ENABLE), U10.5 (VDD)
unnamed: L6.1, R15.2, U10.6 (VSW)
VDD: C21.1, C24.1, C86.1, C90.1, C166.1, C167.1, C168.1, C169.1, L1.2, L6.2; also elsewhere on the board
